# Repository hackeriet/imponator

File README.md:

# Hackeriet Imponator / Badge
Below, you see the layout for the test version, ordered from JLCPCB:

## Distrubutors
When I made these, parts were bought from Digikey or Aliexpress. The PCBs were ordered from JLCPCB. 

## Read the Documentation
The MCU, sensor and USB to UART chip all have datasheets. I recommend having a look at these datasheets.

## Design
To understand the design of this, first open the file "hackeriet_imponator_schematics.pdf". This is the schematic for the PCB. As you can see the design has 6 different sections. The following sub-sections will explain each.

### MCU 
The MCU is the brain of the badge. An MCU is pretty much the same as a CPU, but smaller. For this board, we use the ATtiny804 by Microchip. As a comparison, the Ardino uses the ATmega328P. The name ATtiny804 is put together as such: 

- ATtiny: the name of the MCU family.
- 8: The MCU has 8KB of memory.
- 0: Its the 0-vesion of the ATtiny family.
- 4: Correlates to the pin count. The ATtiny804 has 14 pins.

The MCU has a 100nF capacitor between VCC and GND. This is quite standard for MCUs and sensors, but to be sure, check the datasheet.

There is also two buttons connected to pins, which the user can choose to use as they see fit. 

The UPDI pin is used for flashing the MCU. UDPI is an AVR specific protocol. With this you need just the UPDI pins,and the PCB of course needs to be powered at the same time.

The plan is to program a bootloader on the board once, and then firmware can be pushed over USB.

### RGB LEDs
The RGB LEDs are the WS2812B-4020. They are sideways programmable RGB LEDs, which are aimed into an acryllic plate that will be mounted on top of the PCB. These have four pins. VCC and GND to power the LEDs. Then DIN which is the signal into the LED and DOUT that is the signal out. With this, you can connect multiple LEDs in series, whcih lets you control multiple LEDs with only one pin.

### USB to UART
The MCU does not have USB built-in. Therefore we add a USB to UART converter chip to allow for logging and a bootloader. We use the MCP2221A. This behaves as a bridge between the USB and the MCU, translating USB signals to UART and vice versa. The ATtiny804 only supports UART on specific pins, so the pins for this was decided based on the ATtiny804 datasheet. 
The 5.1k resistors on the CC lines of the USB-C tells the charger/PC connected to the badge that it should deliver 5V over the USB. The 10k resistor on the resistor line is a Pull-Up resistor, as the reset line is active low. 10k is normal for Pull-up resistors. Other passive components come from the datasheet of the MCP2221A.

### Sensor (optional)
The sensor is the MPU-6050. This is an 3-axis gyroscope, 3-axis accelerometer and more. It is connetced to the MCU over the serial protocol I2C. The sensor is not needed for the badge to work, but makes it possible to do some cool stuff with the badge. The downside is that it requires extra parts and is harder to solder than the rest of the badge. The MPU-6050 also runs on a different voltage than the ATtiny. Therefore we use an LDO to convert the power down from 5V to 3.3V. Also, we use transistors as a logic level converter for the I2C bus.

### Power
The badge is powered by either via the USB port or by the battery connector. Tha battery connector is intended for connecting a battery to it. SW1 is used to toggle between battery in via the USB port or via the battery connector. This is to avoid issues if someone connect the battery and the USB at the same time. This means that the switch has to be soldered on for the badge to function correctly.  
Note: Switches are notorious for breaking. In which case it is possible to power the badge via the Shitty Add-on port as a hack.

### Connector
The badge has one external connector, which complies to the Shitty Add-On version one.

## TODO
We will have a soldering course soon. Here is a list of what needs to be prepared

- [x] Get 30x diffusers, both MINUS end BODY
    - [x] Decide diffuser adhesive design
    - [x] Purchase acryllic
- [ ] Count parts we have, and order outstanding
    - [x] USBs
    - [x] Attinys
    - [x] MCP (USB-UART)
    - [ ] Resistors
    - [ ] Capacitors
    - [x] LEDs
    - [x] Buttons
    - [x] Switches
    - [x] Accelerometer
    - [x] LDO
    - [x] Transistors
- [x] Order PCBs
- [x] Receoive PCBs
- [x] Pre-solder LEDs
- [ ] Safety-goggles
- [ ] Fans with carbon filters
- [ ] Write documentation
- [ ] Bring soldering irons

## Building kits

The kits contain some parts to build the imponator.  The resistors and capacitors are not included and need to be taken from the SMD parts books.

### possible build order

- leave film on acrylic, attach to protect leds
- tiny MCP - dot to arrow
- UART - dot to arrow
- R3, R4: 5.1kΩ
- R5 : 10kΩ
- C1, C9: 100nF
- C2: 1µF
- SW2, SW3
- SW1
- USB, place then solder from LED side
- test for short circuits
- program UDPI bootloader
- flash with arduino code in `sw`
- remove acrylic, remove film or scuff with sandpaper for diffuse view
- imponere your friends

### Tips

- practice moving parts around with tweezers
- lower heat: 280C
- small tips are bad at conducting heat
- hot air to remove parts if misplaced
- hot air to help seat USB after soldering
- maybe attach battery

### In the kit

- circuit board with LEDs (handle carefully)
    - if you want to DIY leds with solder paste, ask us
- 2x buttons
- switch
- tiny MCU
- UART
- battery pack
- acrylic plate

### Not in the kit

- resistors
- capacitors
- M2 screws/bolts to attach acrylic plate

### Resistors and Capacitors

| part location | spec |
|---|---|
| R3 R4 | 2x 5.1kΩ |
| R5 | 10kΩ |
| C1 C9 | 2x 100nF |
| C2 | 1µF |
| optional sensors | |
| R6 or R7 | short |
| R8 R9 R10 R11 | 4x 10kΩ |
| C3 | 2.2 nF |
| C4 C5 | 2x 0.1µF |
| C6 | 10 nF |
| C7 C8 | 2x 1µF |

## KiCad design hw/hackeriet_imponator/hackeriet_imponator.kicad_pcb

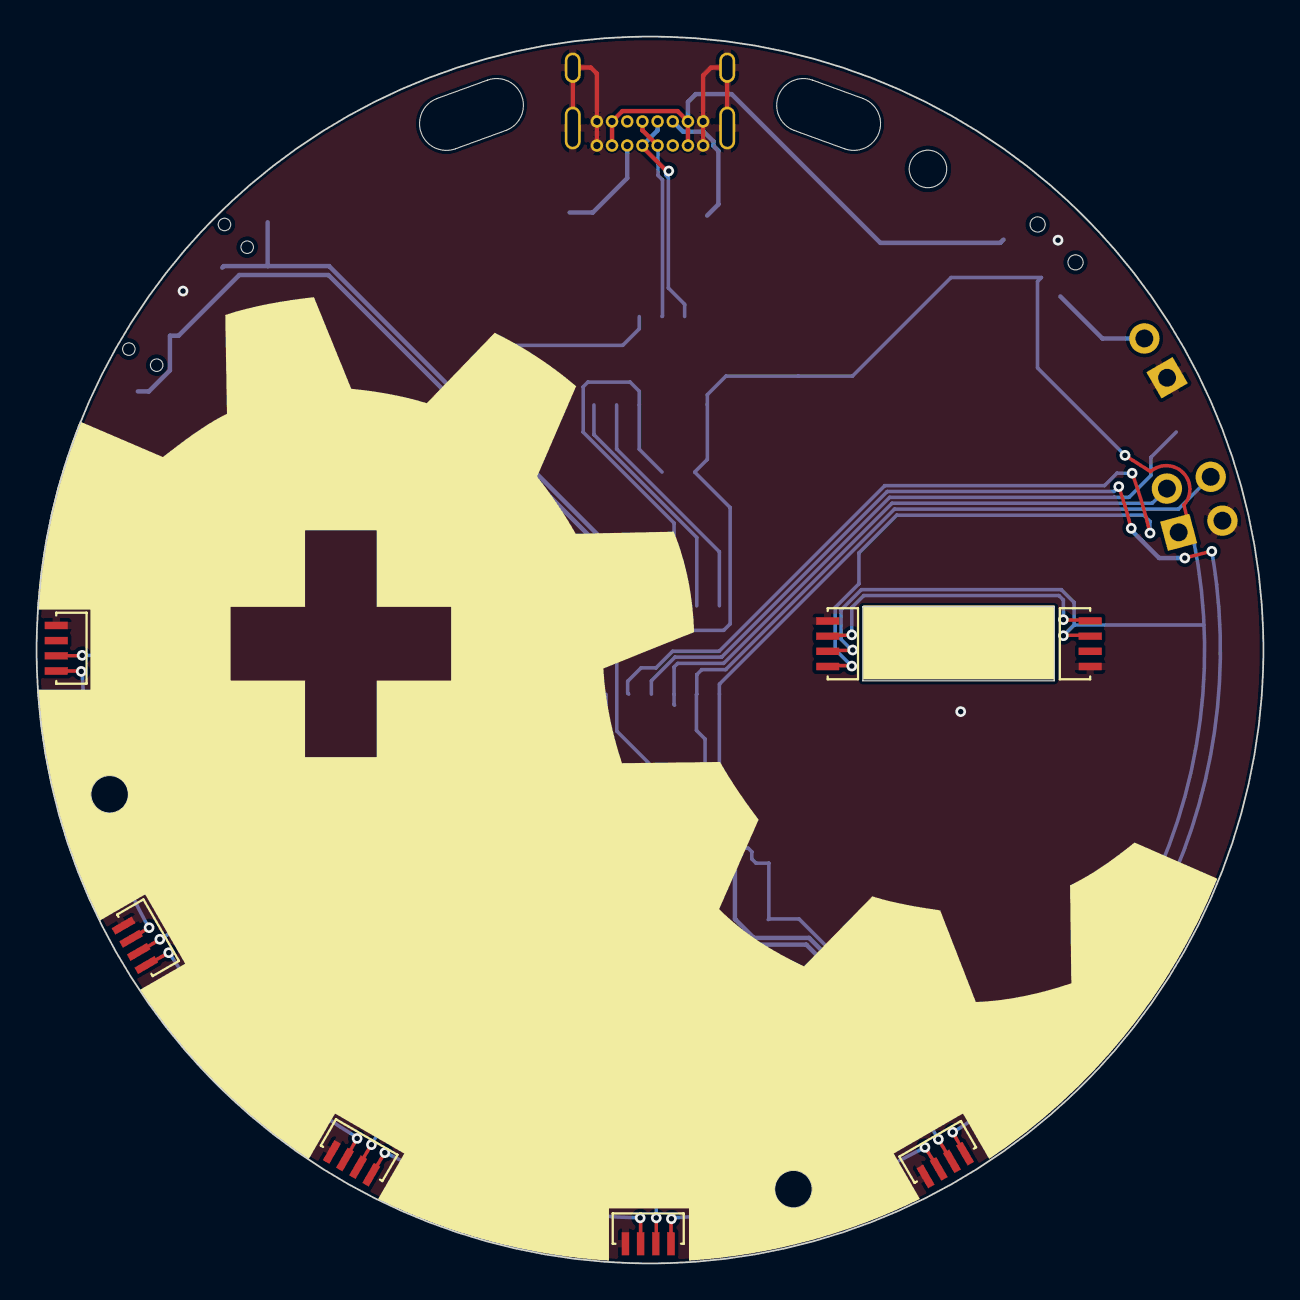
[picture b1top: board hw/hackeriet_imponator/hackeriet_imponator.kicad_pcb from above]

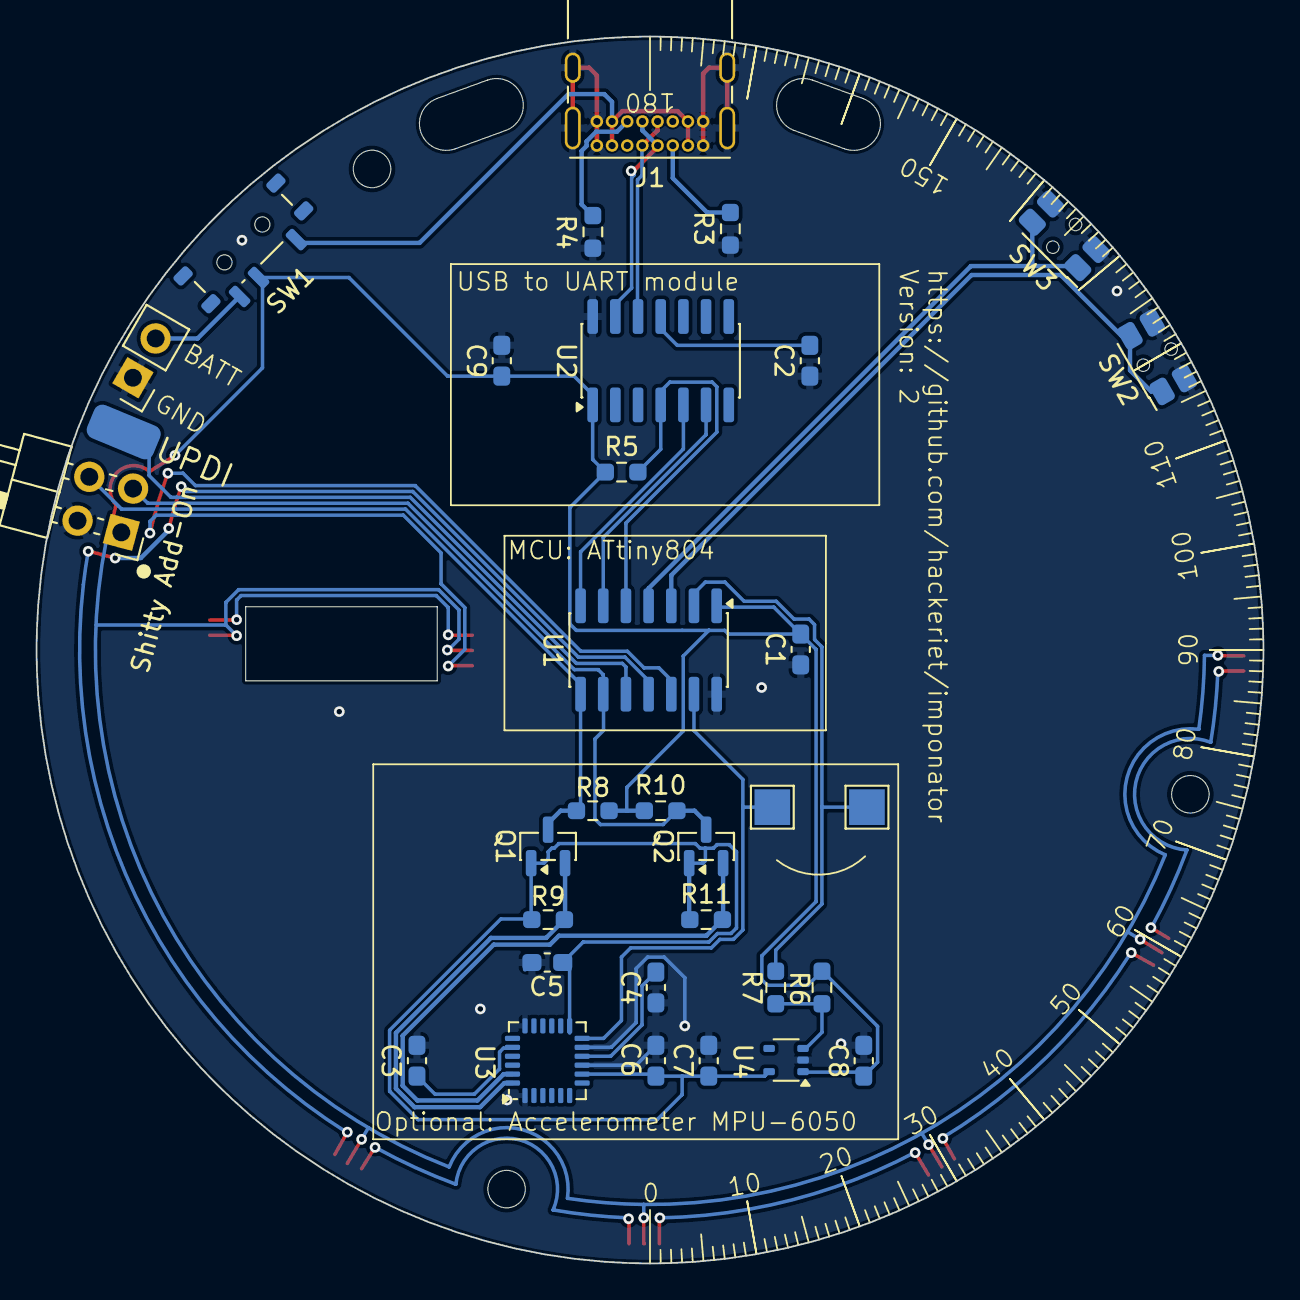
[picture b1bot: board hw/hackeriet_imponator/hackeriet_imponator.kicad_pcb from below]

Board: 2 copper layers, 68.7 x 68.7 mm, 38 parts (31 on the bottom side), 32 nets.

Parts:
C1, C9: 100nF; C_0603_1608Metric_Pad1.08x0.95mm_HandSolder
C2, C7, C8: 1uF; C_0603_1608Metric_Pad1.08x0.95mm_HandSolder
C3: 2.2nF; C_0603_1608Metric_Pad1.08x0.95mm_HandSolder
C4, C5: 0.1uF; C_0603_1608Metric_Pad1.08x0.95mm_HandSolder
C6: 10nF; C_0603_1608Metric_Pad1.08x0.95mm_HandSolder
D1, D2, D3, D4, D5, D6, D7: WS2812B-4020; LED_WS2812B-4020
J1: USB4085-GF-A; USB_C_Receptacle_GCT_USB4085
J2: UPDI programming; SolderWirePad_1x01_SMD_2x4mm
J3: External Battery Connector; PinHeader_1x02_P2.54mm_Vertical
J4: Shitty Add-On; PinHeader_2x02_P2.54mm_Horizontal
Q1, Q2: AO3400A; SOT-23
R3, R4: 5.1K; R_0603_1608Metric_Pad0.98x0.95mm_HandSolder
R5, R8, R9, R10, R11: 10k; R_0603_1608Metric_Pad0.98x0.95mm_HandSolder
R6, R7: 0R; R_0603_1608Metric_Pad0.98x0.95mm_HandSolder
SW1: SW_SPDT; SW_SPDT_Shouhan_MSK12C02
SW2, SW3: User configurable; SW_SPST_EVQP7C
U1: ATtiny804-SS; SOIC-14_3.9x8.7mm_P1.27mm
U2: MCP2221AxSL; SOIC-14_3.9x8.7mm_P1.27mm
U3: MPU-6050; InvenSense_QFN-24_4x4mm_P0.5mm
U4: TLV70028_SOT353; SOT-353_SC-70-5

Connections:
2V8: C5.2, C6.2, C7.1, Q1.1 (G), Q2.1 (G), R9.1, R11.1, U3.8 (VLOGIC), U3.13 (VDD), U4.5 (OUT)
ACC_ENABLE: R7.1, U1.2 (PA4)
ACC_INT: U1.13 (PA3), U3.12 (INT)
Attiny UART RX: U1.6 (PB3), U2.6 (UTx)
Attiny UART TX: U1.7 (PB2), U2.5 (URx)
BATT: J3.2, SW1.3 (C)
D+: J1.A6 (D+), J1.B6 (D+), U2.13 (D+)
D-: J1.A7 (D-), J1.B7 (D-), U2.12 (D-)
GND: C1.1, C2.2, C3.1, C4.1, C5.1, C6.1, C7.2, C8.2, C9.2, D1.4 (VSS), D2.4 (VSS), D3.4 (VSS), D4.4 (VSS), D5.4 (VSS), D6.4 (VSS), D7.4 (VSS), J1.A1 (GND), J1.A12 (GND), J1.B1 (GND), J1.B12 (GND), J1.S1 (SHIELD), J3.1, J4.2, R3.2, R4.2, SW2.2, SW3.2, U1.14 (GND), U2.14 (VSS), U3.1 (CLKIN), U3.9 (AD0), U3.11 (FSYNC), U3.18 (GND), U4.2 (GND)
MCP2221 _RST: R5.2, U1.5 (PA7), U2.4 (~RST)
unnamed: D1.3 (DOUT), D2.1 (DIN)
unnamed: D2.3 (DOUT), D3.1 (DIN)
unnamed: D3.3 (DOUT), D4.1 (DIN)
unnamed: D4.3 (DOUT), D5.1 (DIN)
unnamed: D6.3 (DOUT), D7.1 (DIN)
unnamed: J1.A5 (CC1), R3.1
unnamed: J1.B5 (CC2), R4.1
unnamed: J2.1, U1.10 (~RESET/PA0)
unnamed: Q1.2 (S), R9.2, U3.24 (SDA)
unnamed: Q2.2 (S), R11.2, U3.23 (SCL)
unnamed: SW2.1, U1.3 (PA5)
unnamed: SW3.1, U1.4 (PA6)
unnamed: C2.1, U2.11 (VUSB)
unnamed: C3.2, U3.20 (CPOUT)
unnamed: C4.2, U3.10 (REGOUT)
unnamed: R6.2, R7.2, U4.3 (EN)
SCL: J4.3, Q2.3 (D), R10.2, U1.9 (PB0)
SDA: J4.4, Q1.3 (D), R8.2, U1.8 (PB1)
USB_VDD: J1.A4 (VBUS), J1.A9 (VBUS), J1.B4 (VBUS), J1.B9 (VBUS), SW1.1 (A)
VDD: C1.2, C8.1, C9.1, D1.2 (VDD), D2.2 (VDD), D3.2 (VDD), D4.2 (VDD), D5.2 (VDD), D6.2 (VDD), D7.2 (VDD), J4.1, R5.1, R6.1, R8.1, R10.1, SW1.2 (B), U1.1 (VCC), U2.1 (VDD), U4.1 (IN)
WS2812B LED RGB Control logo: D1.1 (DIN), U1.11 (PA1)
WS2812B LED RGB Control minus: D6.1 (DIN), U1.12 (PA2)

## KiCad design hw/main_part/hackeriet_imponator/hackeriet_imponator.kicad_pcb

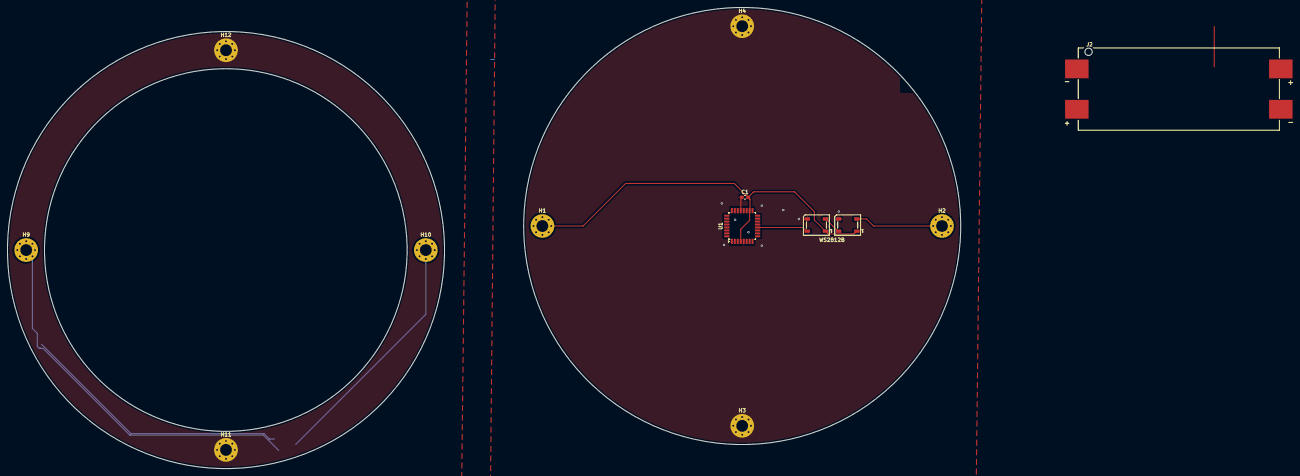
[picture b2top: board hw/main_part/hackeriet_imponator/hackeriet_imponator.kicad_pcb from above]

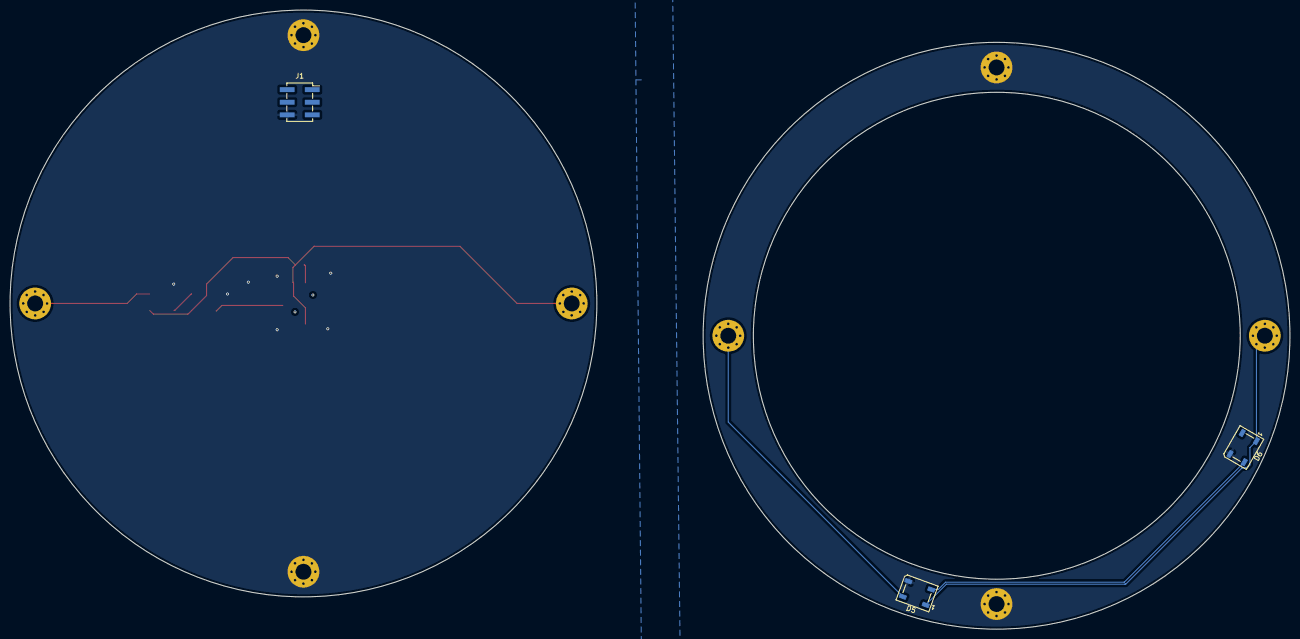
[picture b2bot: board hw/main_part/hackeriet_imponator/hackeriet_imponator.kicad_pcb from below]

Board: 2 copper layers, 257.6 x 124.6 mm, 16 parts (3 on the bottom side), 12 nets.

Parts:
C1: 100nF; C_0603_1608Metric_Pad1.08x0.95mm_HandSolder
D1, D2, D5, D6: WS2812B; LED_WS2812B_PLCC4_5.0x5.0mm_P3.2mm
H1, H2, H3, H4, H9, H10, H11, H12: MountingHole_Pad; MountingHole_3.2mm_M3_Pad_Via
J1: AVR-ISP-6; PinSocket_2x03_P2.54mm_Vertical_SMD
J2: Battery connector; BAT_1022
U1: ATmega328PB-A; TQFP-32_7x7mm_P0.8mm

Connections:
+3.3V: C1.2, D1.1 (VDD), D2.1 (VDD), D5.1 (VDD), D6.1 (VDD), H1.1, H9.1, J1.2 (VCC), J2.1, U1.4 (VCC), U1.18 (AVCC)
GND: C1.1, D1.3 (VSS), D2.3 (VSS), D5.3 (VSS), D6.3 (VSS), H3.1, H4.1, H11.1, H12.1, J1.6 (GND), J2.3, U1.5 (GND), U1.21 (GND)
unnamed: D1.4 (DIN), U1.12 (PB0)
unnamed: D1.2 (DOUT), D2.4 (DIN)
unnamed: D2.2 (DOUT), H2.1
unnamed: D5.4 (DIN), H10.1
unnamed: D5.2 (DOUT), D6.4 (DIN)
unnamed: J1.1 (MISO), U1.16 (PB4)
unnamed: J1.4 (MOSI), U1.15 (PB3)
unnamed: J1.3 (SCK), U1.17 (PB5)
unnamed: J1.5 (~RST), U1.29 (~RESET/PC6)
unnamed: J2.2, J2.4

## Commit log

2025-08-14 Added gitignore
2025-08-23 Added MCU and some LEDs for main part.
    TODO: Battery holder and top ring
2025-08-24 Added some external components for battery holders
2025-08-24 Added ring. Added programming header. Started with batt connector
2025-08-24 Moved things around to clean up
2025-08-24 Added Batttery holders. Some general routing
2025-08-24 Started changing out ATmega328P with ATmega32URC because the latter got built-in USB driver, making the design easier, if a bit more expensive
2025-08-24 Imported SVG of logo directly to line stuff up better. Also better silkscreen.
2025-09-03 Added cutout
2025-10-05 Resized logo and made it into part
2025-10-05 Major change. Resized PCB. Changed CPU. Added USB. Added headers. Added another layer for batteries
2025-10-05 Added paneling with mouse bites
2025-10-05 Added final touches. This version will be ordered
2025-10-05 Regenerated gerbers without silkscreen on pads. When I said 'will be ordered' last commit, I mean just a test batch.
2025-10-06 Added image of JLCPCB model to be able to show this off
2025-10-06 Added holes to plate model. Also generated DXF, in case its needed for production.
2025-10-06 Added image to README
2025-10-06 Added explanation
2025-10-06 Added TODO
2025-10-06 Two more TODOs, on silkscreen improvements.
2025-10-11 Added spreadsheet to see costs. Waiting for some costs still
2025-10-11 Improved DXF
2025-10-13 Removed secondary source, as it was too expensive. Added Vendor, and some vendor codes
2025-10-21 Added todo for power source switch
2025-10-21 Added TODO for button
2025-10-23 Added schematics as PDF
2025-10-23 Added footprint as well.
2025-10-24 Added more things to imrove
2025-10-26 Add TODO for sideways LEDs
2025-11-04 Added more TODOs
2025-11-04 MOre TODOs
2025-11-23 Removed outer ring and battery backplate. Ready to apply TODOs
2025-11-23 Dont want backplate, will reduce complexity
2025-11-23 Added switch between batt and USB. Changed LEDs to sideways
2025-11-23 Edited logo to have space for sideways LEDs
2025-11-23 Fine-tuned silkscreen logo and LED spacing.
2025-11-23 Added design rules from JLCPCB
2025-11-24 Added accelerometer to schematic. Also crossed off some TODOs that were already done.
2025-11-29 Added LDO for accelerometer
2025-11-30 Fixed LED pinout. Added PCB button. Distributed headers along side.
2025-11-30 Added holes to design
2025-11-30 Did a bunch of routing and changed holes. Also some silk
2025-11-30 More routing
2025-12-03 Added Logic Level Converter. Added GND vias. Routed the rest. Ran Design Rules test and fixed stuff.
2025-12-04 Cleaned up silkscreen. Added some more silkscreen stuff.
2025-12-04 Some cleanup
2025-12-04 Revision 2 ready for ordering
2026-04-14 Decided on diffuser
2026-04-14 Updated costs list. Added todo for course
2026-04-21 Got PCBs
2026-04-21 Added acryllic cost. This seems to be the final one
2026-04-21 Updated schematic
2026-04-21 Started doing documentation
2026-05-05 Finished readme
2026-05-05 Added software.
2026-05-09 Fixed pin number
2026-05-18 README instructions
2026-05-26 Added bootloader hex
2026-05-26 Added fuses docs
2026-05-26 Elaborated on the bootloader
